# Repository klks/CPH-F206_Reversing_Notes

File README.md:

# How it started
Late 2025, I came across a Taobao listing that was selling a UHF RFID Reader for less than 10USD, this is fairly uncommon as most readers go for 15+usd onwards. I decided to buy one to add to my reader collection. (I ended up buying 6 units)<br>

<br>

This UHF RFID reader is sold under the model numbers below (with Taobao links)

- [CPH-F206](https://item.taobao.com/item.htm?id=904352296655&skuId=5763416697782)
- [TC-C206](https://item.taobao.com/item.htm?id=820590020134&skuId=5696639435762)
- [BYH-206](https://detail.tmall.com/item.htm?id=986978403603&skuId=5952377616135)

Searching online based on provided software, and screenshots, I was able to track down the company that made the software to [Cykeo](https://www.cykeorfid.com/), they are a company that specializes in making industrial rfid readers and antennas.

# Reader Software
The reader comes with its own software and SDK, and is able to output in multiple formats including Wiegand, Modbus, as well as emulating a USB Keyboard.<br>
<br>
<br>

# PCB Screenshot
Cracking open the reader, we are greeted with a 30mm x 30mm PCB soldered to a another PCB that provides a USB-C connector, a buzzer, and some led's, to keep the PCB compact, 0603 SMD components were used.<br>
<br>

Taking a closer look at the front, we see the MCU and an unknown RF chip has their markings lasered off, and the back has descriptions on what each pin does, what catches my eye is the SWDIO and SWCLK pins, this means theres Serial Wire Debug capabilities, and a chance to dump firmware.<br>
<br>
<br>

# MCU Identification & Firmware Dumping
Before we can attempt to dump the firmware, we'd need to try to figure out what MCU is used, and lucky for us when plugging in the reader the device identifies itself as a N32g43xCustom HID, this led me to believe that the MCU was a [N32G435](https://nsing.com.sg/product/General/cortexm4/N32G435/)

Connecting the SWD header to a J-LINK, setting up its parameters, and attempting to read the firmware, I was able to get a successful dump. Usually MCU's have code readout protection which prevents the downloading of flash contents, the manufacturer did not turn this feature on.

# Firmware Reversing
The firmware can now be thrown into IDA/Ghidra for analysis, using the strings within, around 70% of the firmware can be mapped back to the N32G43x SDK and example implementation found on github. From within the firmware, the RF chip can be identified, they are using an [Si4463](https://www.silabs.com/wireless/proprietary/ezradiopro-sub-ghz-ics/device.si4463?tab=specs) Transceiver chip that supports the ISM band.

<br>
The reversing of the firmware is left as an exercise for the user and will not be covered here.

# PCB Reverse Engineering
The reversing of the PCB would not be possible if the firmware dump was not successful, now that we have the firmware, my next goal is to recreate the PCB but using larger 0805 SMD components.

With PCB reversing, the first steps are component identification, using a hot-plate, components were removed one by one, and their values recorded.<br>

<br>

When dealing with small value components like inductors and capacitors, a Nano-VNA can be used to identify their values.<br>

<br>

# Parts Identification
Identification of parts took a while as finding parts with the same name was challenging. Using part numbers, a multimeter, a component tester, an oscilloscope, image searching and pouring over datasheets helped find most of the components.<br>

<br>

| Marking | Name | Notes |
| --- | ---| --- |
| N32G435 | | MCU <br> [Datasheet](https://www.nsing.com.sg/uploads/DS/EN_DS_N32G435.pdf) |
| Si4463 | | RF Transceiver <br> [Datasheet](https://www.silabs.com/documents/public/data-sheets/Si4463-61-60-C.pdf)|
| 87t | Planar Schottky barrier diode |  [1PS70SB84](https://assets.nexperia.com/documents/data-sheet/1PS70SB82_84_85_86.pdf) (Obsolete), the closest is [BAT54S](https://assets.nexperia.com/documents/data-sheet/BAT54S.pdf) |
| 1F | 45 V, 100 mA NPN/NPN general-purpose transistor | [Datasheet](https://assets.nexperia.com/documents/data-sheet/BC847BS.pdf) |
| -V4 | 2-ch, 1.65-V to 5.5-V inverters | [SN74LVC2G04](https://www.ti.com/lit/ds/symlink/sn74lvc2g04.pdf) |
| AM | NPN switching transistor | [MMBT3904](https://www.onsemi.com/pdf/datasheet/mmbt3904wt1-d.pdf) |
| G4B | RF Switching Diode | No exact match found, the closest is [BAV70](https://assets.nexperia.com/documents/data-sheet/BAV70.pdf)
| N933 | 500mA uCap Ultra-Low Dropout, High PSRR LDO Regulator | [Datasheet](https://ww1.microchip.com/downloads/aemDocuments/documents/OTH/ProductDocuments/DataSheets/500mA-uCap-Ultra-Low-Dropout-Regulator-with-High-PSRR-DS20005876B.pdf) |

For the Si4463 matching and filter network, the datasheet was used to identify the nominal values.

<br>

# Sanding PCB
After the components and their positions have been identified, the solder mask of the PCB is stripped using a 200-600 grit sandpaper to expose the front and back copper layers. This PCB is 4 layers and is 1mm thick.

<br>
<br>

# Tracing PCB
Next using high resolution images, Inkscape, and a multimeter, the traces of the PCB and its via's are drawn in separate layers<br>
This step also maps the MCU and RF pins, an overlay from the datasheet is added for pin identification. The position and values of components measured earlier are also noted, grounds and power lines (5V, 3V3) are color coded.<br>

<br>

<br>

# Reversing PCB & Schematic
Using KiCad, the schematic is then redrawn with their component values. In this step, the component names from KiCad are mapped back to the PCB Trace in Inkscape. Some modifications were made around the USB-C and 3V3 power regulators circuit.

<br>

Schematics are released in the schematic directory of this repo.

# Impedance Matching of RF Trace
When recreating the PCB, KiCad's Calculator Tools and JLCPCB's Capabilities are used to calculate trace width and spacing for the RF trace line.

<br>
<br>

# Ordering & Testing PCB
After weeks of tracing and schematic drawing, PCB's are sent for fabrication. When placing components, i mimicked the layout of the original board, this was done to make circuit debugging easier<br>
<br>
Below is a size comparison of the original and recreated PCB.<br>
<br>
After soldering all the components, the original MCU was soldered on for testing. In the first attempt, the reader was not picking up any tags.<br>
Going back to the drawing board, a few components had to be re-measured from another working reader and a few mistakes were identified. At this point an oscilloscope was used to debug the circuit using references from a functional reader. After fixing mis-typed components and much experimenting, the reader works!.<br>
<br>
One area that needs to be studied more is the matching network and filter sections as the current PCB isn't as fast/sensitive enough at picking up tags vs the original reader.<br>
In v0.2 of the schematic, additional capacitors were added to the 5V rail. Also fixed incorrectly measured value for some components.<br>

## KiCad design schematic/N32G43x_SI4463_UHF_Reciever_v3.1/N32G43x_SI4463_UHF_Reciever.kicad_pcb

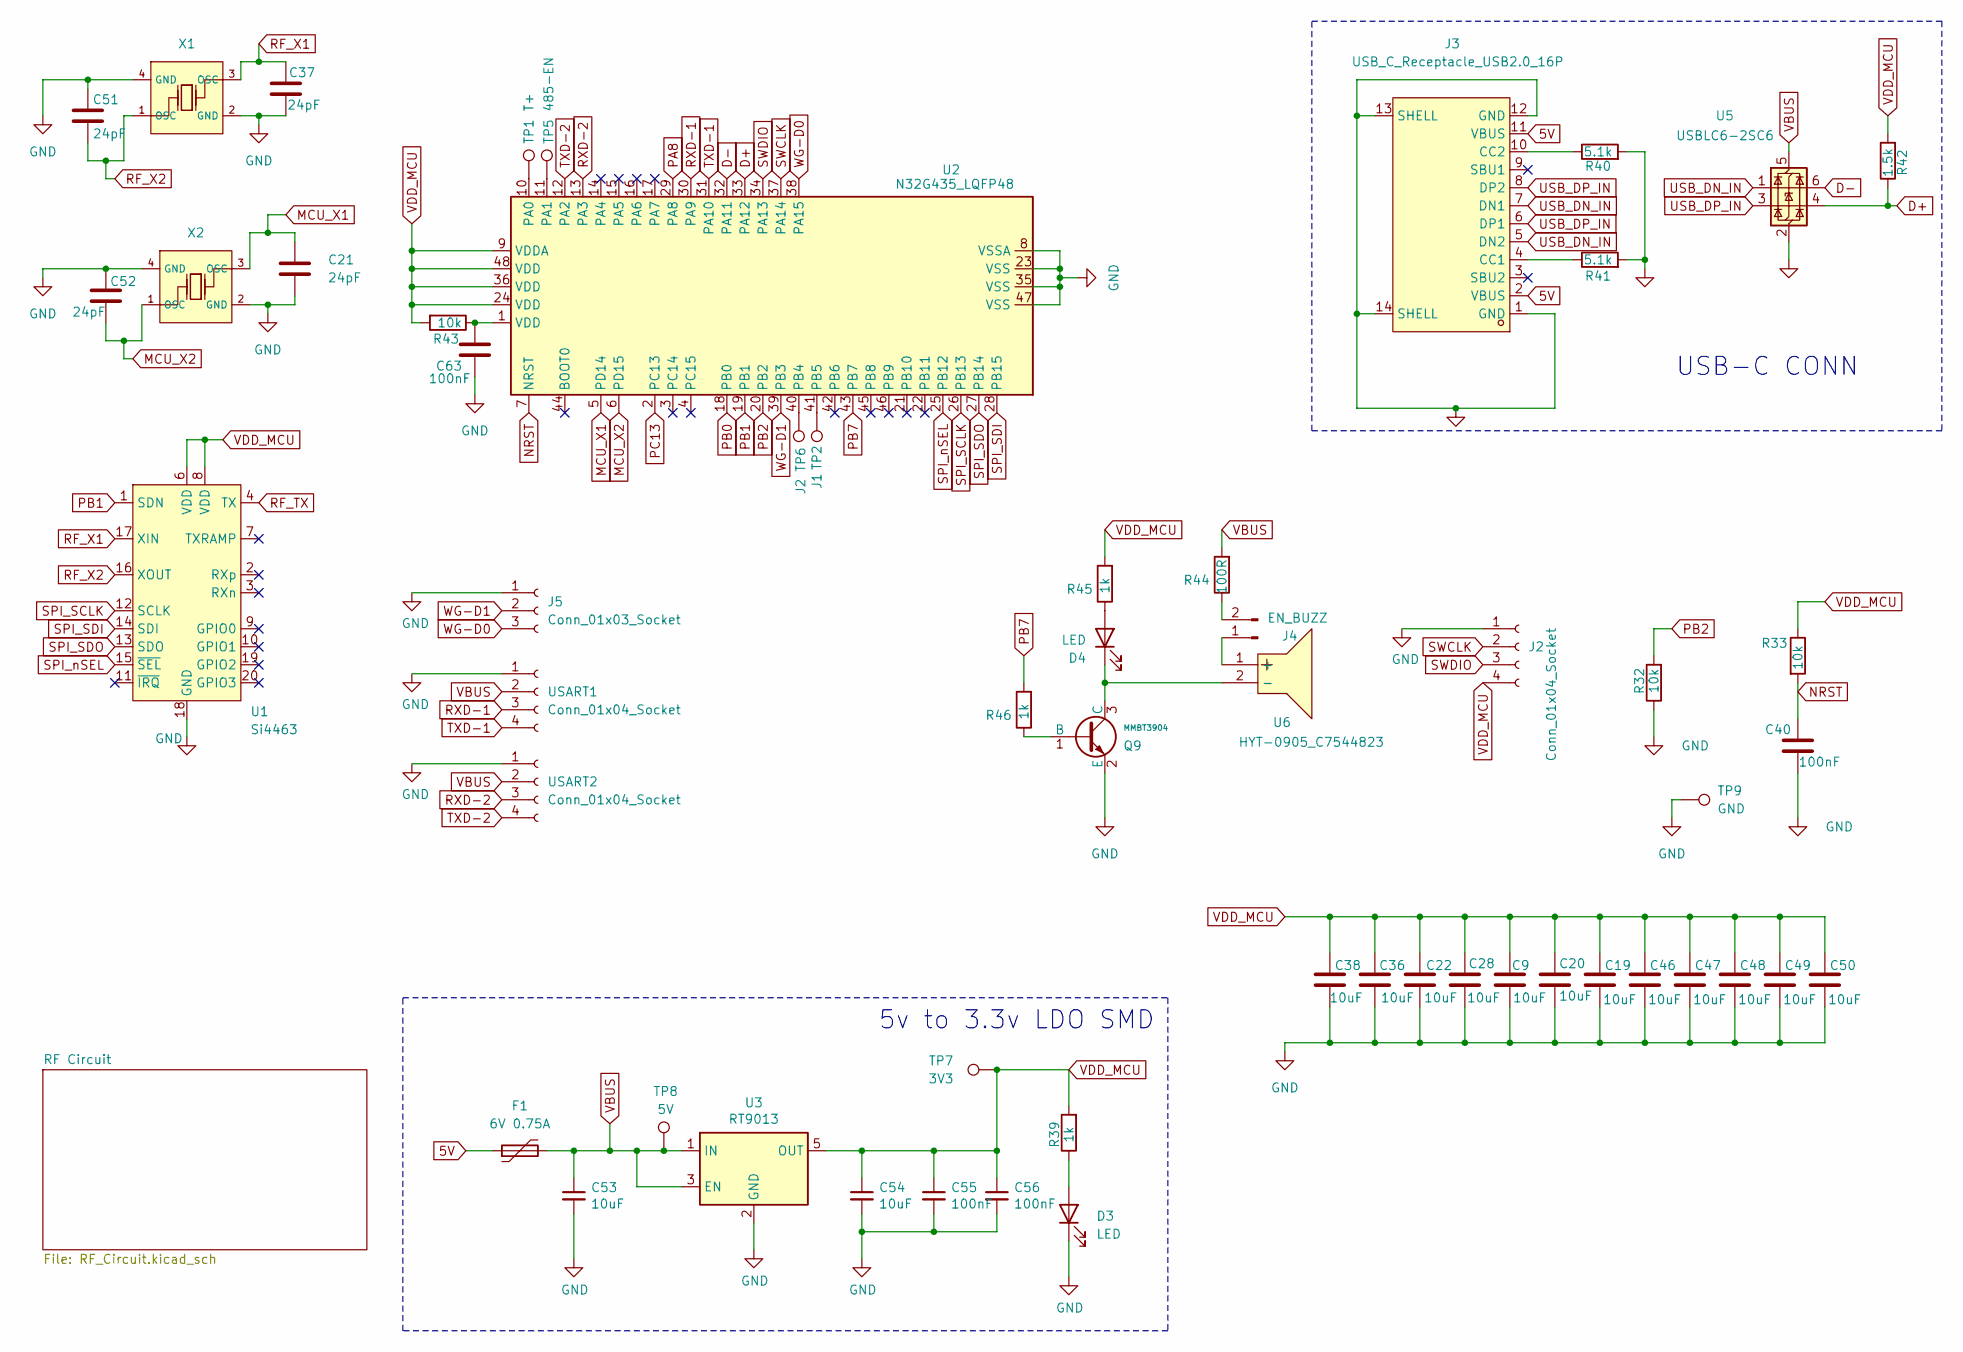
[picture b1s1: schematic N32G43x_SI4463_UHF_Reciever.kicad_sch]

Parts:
C9, C19, C20, C22, C28, C36, C38, C46, C47, C48, C49, C50, C53, C54: 10uF; C_0805_2012Metric_Pad1.18x1.45mm_HandSolder
C21, C37, C51, C52: 24pF; C_0805_2012Metric_Pad1.18x1.45mm_HandSolder
C40, C55, C56, C63: 100nF; C_0805_2012Metric_Pad1.18x1.45mm_HandSolder
D3, D4: LED; LED_0805_2012Metric_Pad1.15x1.40mm_HandSolder
F1: 6V 0.75A; Fuse_0805_2012Metric_Pad1.15x1.40mm_HandSolder
J2: Conn_01x04_Socket; PinHeader_1x04_P2.54mm_Vertical
J3: USB_C_Receptacle_USB2.0_16P; USB-C-SMD_TYPE-C-6PIN-2MD-073; LCSC Part C2765186
J4: EN_BUZZ; SolderJumper-2_P1.3mm_Open_RoundedPad1.0x1.5mm
J5: Conn_01x03_Socket; PinHeader_1x03_P2.54mm_Vertical
Q9: MMBT3904; Q_SOT-23; Part MMBT3904; LCSC C7420353
R32, R33, R43: 10k; R_0805_2012Metric_Pad1.20x1.40mm_HandSolder
R39, R45, R46: 1k; R_0805_2012Metric_Pad1.20x1.40mm_HandSolder
R40, R41: 5.1k; R_0805_2012Metric_Pad1.20x1.40mm_HandSolder
R42: 1.5k; R_0805_2012Metric_Pad1.20x1.40mm_HandSolder
R44: 100R; R_0805_2012Metric_Pad1.20x1.40mm_HandSolder
TP1: T+; TestPoint_Pad_D1.5mm
TP2: J1; TestPoint_Pad_D1.5mm
TP5: 485-EN; TestPoint_Pad_D1.5mm
TP6: J2; TestPoint_Pad_D1.5mm
TP7: 3V3; TestPoint_Pad_D1.5mm
TP8: 5V; TestPoint_Pad_D1.5mm
TP9: GND; TestPoint_Pad_D1.5mm
U1: Si4463; QFN-20-1EP_4x4mm_P0.5mm_EP2.6x2.6mm_ThermalVias
U2: N32G435_LQFP48; LQFP-48_7x7mm_P0.5mm; Operating Voltage Range 2V~3.6V; Low Voltage Detection T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 2V~3.6V; Part STM32F103C8T6; LCSC C8734
U3: RT9013; TSOP-5_1.65x3.05mm_P0.95mm
U5: USBLC6-2SC6; SOT-23-6
U6: HYT-0905_C7544823; BUZ-TH_BD9.0-P5.00-D0.6-FD; LCSC Part C7544823
USART1, USART2: Conn_01x04_Socket; PinHeader_1x04_P2.54mm_Vertical
X1, X2: X322525MOB4SI; OSC-SMD_4P-L3.2-W2.5-BL; Frequency Tolerance ±10ppm; Part X322525MOB4SI; LCSC C9006

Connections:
5V: F1.1, J3.2 (VBUS), J3.11 (VBUS)
D+: R42.1, U2.33 (PA12), U5.4 (I/O2)
D-: U2.32 (PA11), U5.6 (I/O1)
MCU_X1: C21.1, U2.5 (PD14), X2.3 (OSC)
MCU_X2: C52.2, U2.6 (PD15), X2.1 (OSC)
NRST: C40.2, R33.2, U2.7 (NRST)
unnamed: C63.1, R43.1, U2.1 (VDD)
unnamed: D3.2 (A), R39.1
unnamed: D4.2 (A), R45.1
unnamed: D4.1 (K), Q9.3 (C), U6.2 (-)
unnamed: J3.4 (CC1), R41.1
unnamed: J3.10 (CC2), R40.1
unnamed: J4.1, U6.1 (+)
unnamed: J4.2, R44.1
unnamed: Q9.1 (B), R46.1
unnamed: TP1.1, U2.10 (PA0)
unnamed: TP5.1, U2.11 (PA1)
unnamed: TP6.1, U2.40 (PB4)
unnamed: TP2.1, U2.41 (PB5)
PA8: U2.29 (PA8); also elsewhere on the board
PB0: U2.18 (PB0); also elsewhere on the board
PB1: U1.1 (SDN), U2.19 (PB1)
PB2: R32.2, U2.20 (PB2)
PB7: R46.2, U2.43 (PB7)
PC13: U2.2 (PC13); also elsewhere on the board
RF_TX: U1.4 (TX); also elsewhere on the board
RF_X1: C37.1, U1.17 (XIN), X1.3 (OSC)
RF_X2: C51.2, U1.16 (XOUT), X1.1 (OSC)
RXD-1: U2.30 (PA9), USART1.3
RXD-2: U2.13 (PA3), USART2.3
SPI_SCLK: U1.12 (SCLK), U2.26 (PB13)
SPI_SDI: U1.14 (SDI), U2.28 (PB15)
SPI_SDO: U1.13 (SDO), U2.27 (PB14)
SPI_nSEL: U1.15 (~SEL), U2.25 (PB12)
SWCLK: J2.2, U2.37 (PA14)
SWDIO: J2.3, U2.34 (PA13)
TXD-1: U2.31 (PA10), USART1.4
TXD-2: U2.12 (PA2), USART2.4
USB_DN_IN: J3.5 (DN2), J3.7 (DN1), U5.1 (I/O1)
USB_DP_IN: J3.6 (DP1), J3.8 (DP2), U5.3 (I/O2)
VBUS: C53.1, F1.2, R44.2, TP8.1, U3.1 (IN), U3.3 (EN), U5.5 (VBUS), USART1.2, USART2.2; also elsewhere on the board
VDD_MCU: C9.2, C19.1, C20.1, C22.1, C28.2, C36.1, C38.1, C46.1, C47.1, C48.1, C49.1, C50.1, C54.1, C55.1, C56.1, J2.4, R33.1, R39.2, R42.2, R43.2, R45.2, TP7.1, U1.6 (VDD), U1.8 (VDD), U2.9 (VDDA), U2.24 (VDD), U2.36 (VDD), U2.48 (VDD), U3.5 (OUT); also elsewhere on the board
WG-D0: J5.3, U2.38 (PA15)
WG-D1: J5.2, U2.39 (PB3)

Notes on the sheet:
5v to 3.3v LDO SMD
USB-C CONN

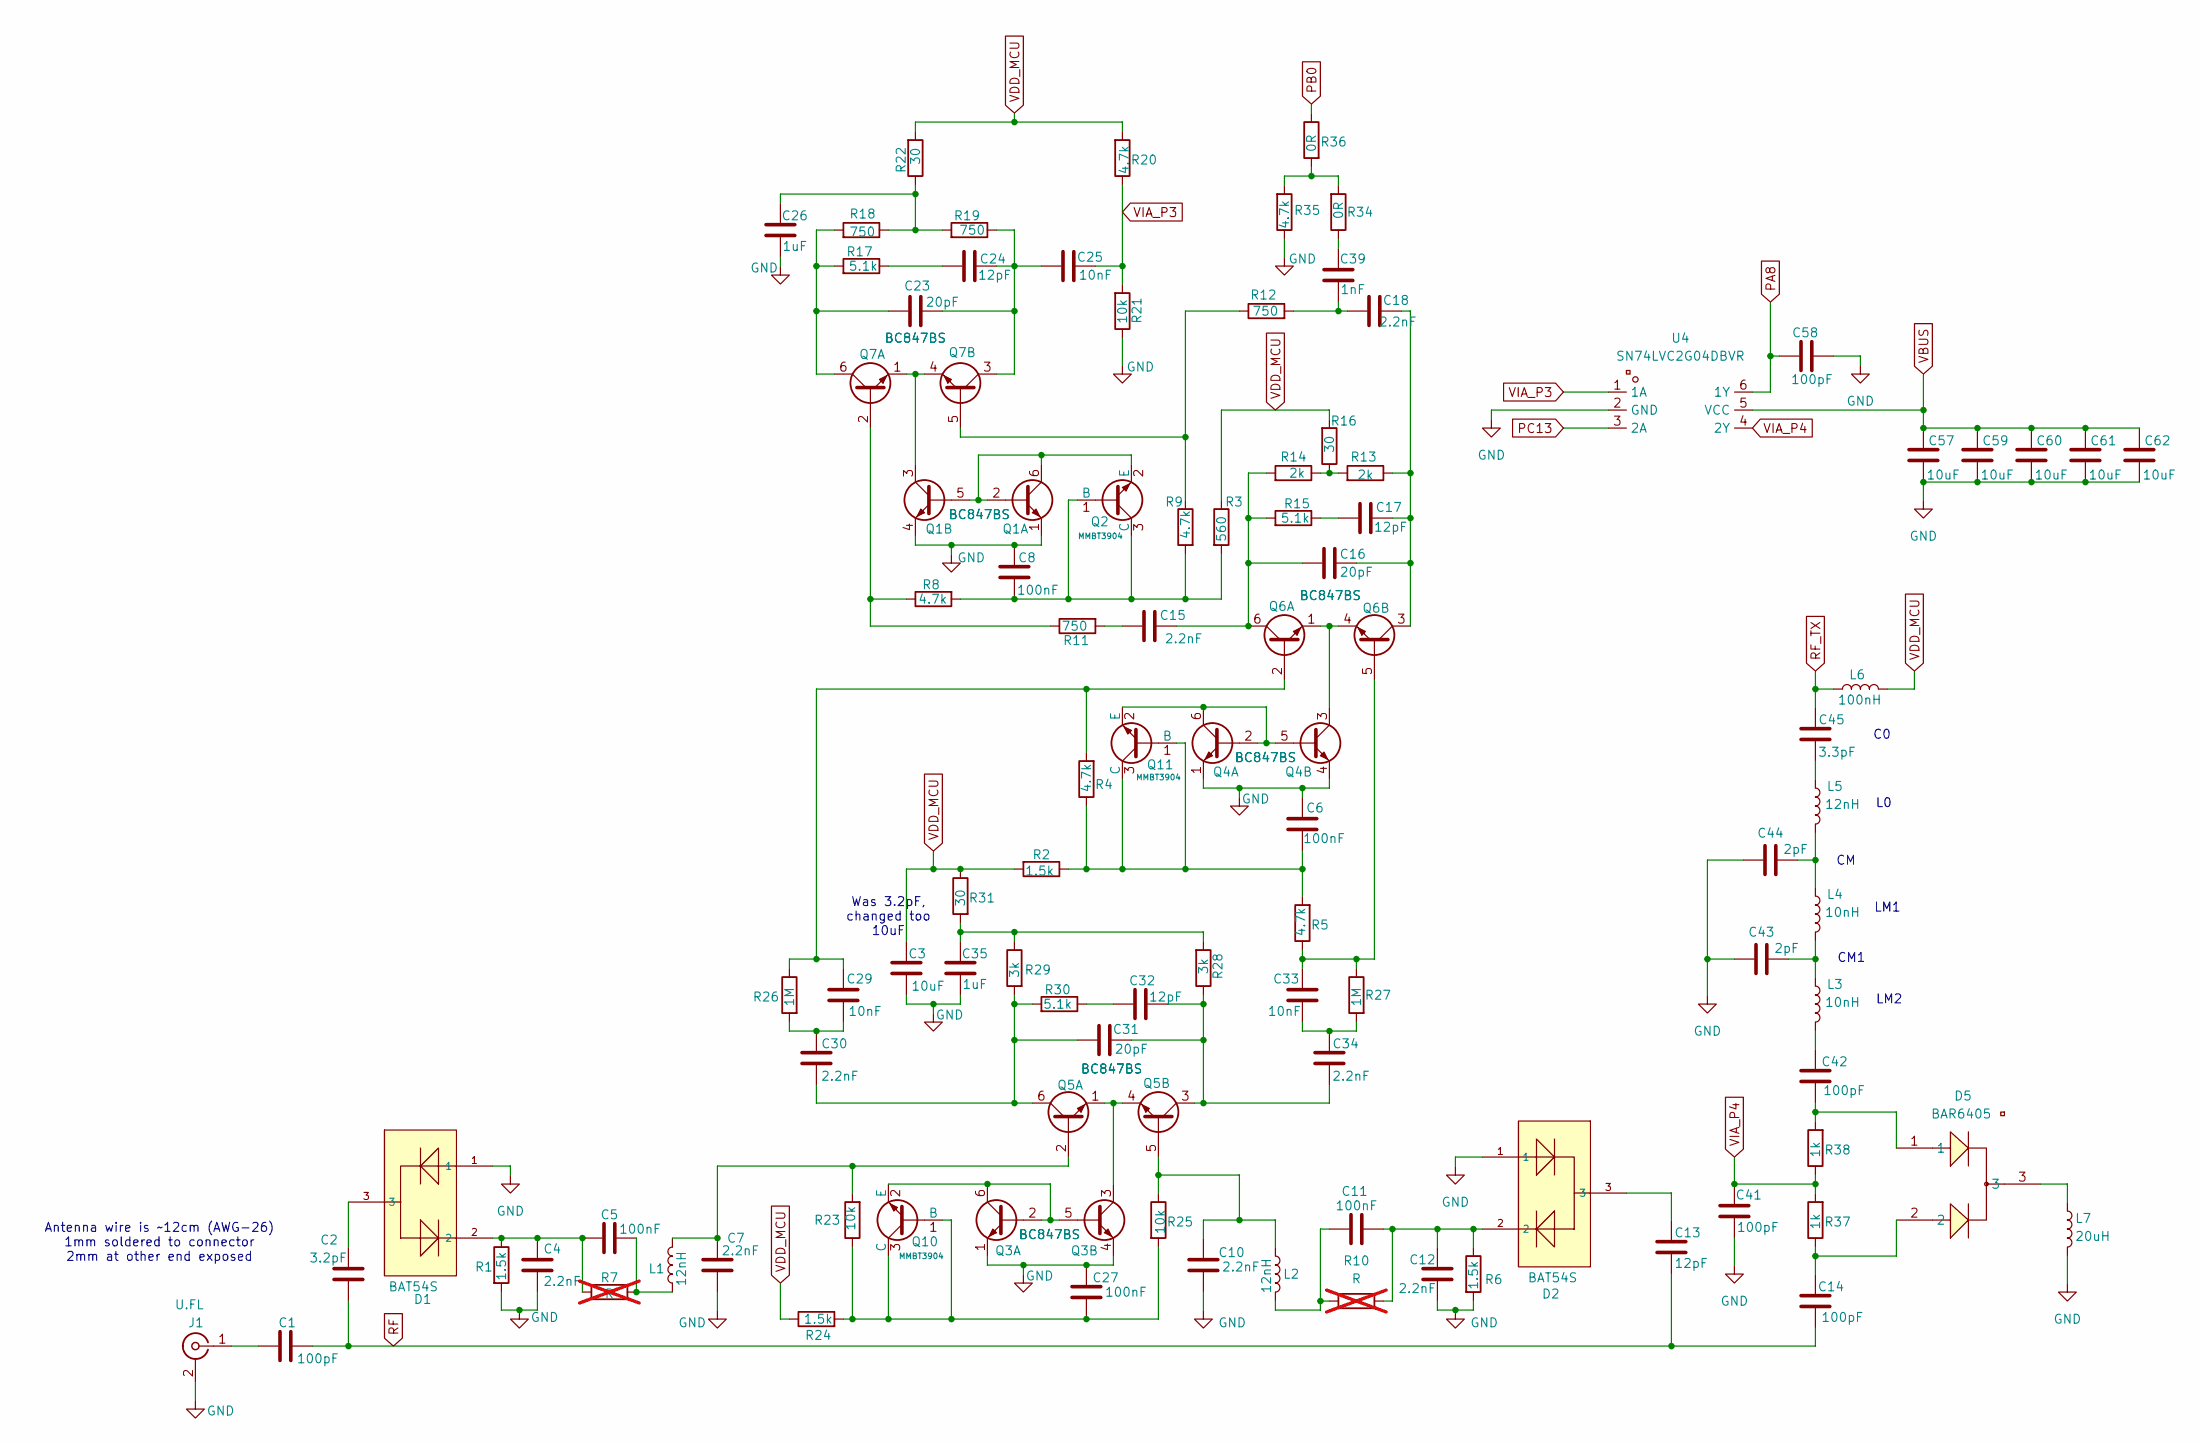
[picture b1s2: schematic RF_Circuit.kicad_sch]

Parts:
C1, C14, C41, C42, C58: 100pF; C_0805_2012Metric_Pad1.18x1.45mm_HandSolder
C2: 3.2pF; C_0805_2012Metric_Pad1.18x1.45mm_HandSolder
C3: 10uF; C_0805_2012Metric_Pad1.18x1.45mm_HandSolder
C4, C7, C10, C12, C15, C18, C30, C34: 2.2nF; C_0805_2012Metric_Pad1.18x1.45mm_HandSolder
C5, C6, C8, C11, C27: 100nF; C_0805_2012Metric_Pad1.18x1.45mm_HandSolder
C13, C17, C24, C32: 12pF; C_0805_2012Metric_Pad1.18x1.45mm_HandSolder
C16, C23, C31: 20pF; C_0805_2012Metric_Pad1.18x1.45mm_HandSolder
C25, C29, C33: 10nF; C_0805_2012Metric_Pad1.18x1.45mm_HandSolder
C26, C35: 1uF; C_0805_2012Metric_Pad1.18x1.45mm_HandSolder
C39: 1nF; C_0805_2012Metric_Pad1.18x1.45mm_HandSolder
C43, C44: 2pF; C_0805_2012Metric_Pad1.18x1.45mm_HandSolder
C45: 3.3pF; C_0805_2012Metric_Pad1.18x1.45mm_HandSolder
C57, C59, C60, C61, C62: 10uF; C_1206_3216Metric_Pad1.33x1.80mm_HandSolder
D1, D2: BAT54S; SOT-23-3_L2.9-W1.6-P1.90-LS2.8-BR; Reverse Voltage (Vr) 100V; Forward Voltage (Vf@If) 1.25V@150mA; Part BAV99,215
D5: BAR6405; SOT-23-3_L2.9-W1.6-P1.90-LS2.8-BR
J1: U.FL; IPEX-SMD_BWIPX-1-001E; LCSC C5137195
L1, L2, L5: 12nH; L_0805_2012Metric_Pad1.05x1.20mm_HandSolder
L3, L4: 10nH; L_0805_2012Metric_Pad1.05x1.20mm_HandSolder
L6: 100nH; L_0805_2012Metric_Pad1.05x1.20mm_HandSolder
L7: 20uH; L_0805_2012Metric_Pad1.05x1.20mm_HandSolder
Q1, Q3, Q4, Q5, Q6, Q7: BC847BS; SOT-363_SC-70-6; Part BC847BS; LCSC C41375126
Q2, Q10, Q11: MMBT3904; Q_SOT-23; Part MMBT3904; LCSC C7420353
R1, R2, R6, R24: 1.5k; R_0805_2012Metric_Pad1.20x1.40mm_HandSolder
R3: 560; R_0805_2012Metric_Pad1.20x1.40mm_HandSolder
R4, R5, R8, R9, R20, R35: 4.7k; R_0805_2012Metric_Pad1.20x1.40mm_HandSolder
R7, R10: R; R_0805_2012Metric_Pad1.20x1.40mm_HandSolder; not fitted
R11, R12, R18, R19: 750; R_0805_2012Metric_Pad1.20x1.40mm_HandSolder
R13, R14: 2k; R_0805_2012Metric_Pad1.20x1.40mm_HandSolder
R15, R17, R30: 5.1k; R_0805_2012Metric_Pad1.20x1.40mm_HandSolder
R16, R22, R31: 30; R_0805_2012Metric_Pad1.20x1.40mm_HandSolder
R21, R23, R25: 10k; R_0805_2012Metric_Pad1.20x1.40mm_HandSolder
R26, R27: 1M; R_0805_2012Metric_Pad1.20x1.40mm_HandSolder
R28, R29: 3k; R_0805_2012Metric_Pad1.20x1.40mm_HandSolder
R34, R36: 0R; R_0805_2012Metric_Pad1.20x1.40mm_HandSolder
R37, R38: 1k; R_0805_2012Metric_Pad1.20x1.40mm_HandSolder
U4: SN74LVC2G04DBVR; SOT-23-6_L2.9-W1.6-P0.95-LS2.8-BR; LCSC Part C10428

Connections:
unnamed: C2.2, D1.3
unnamed: C4.2, C5.2, D1.2, R1.1, R7.1
unnamed: C5.1, L1.1, R7.2
unnamed: C11.1, C12.2, D2.2, R6.1, R10.2
unnamed: C11.2, L2.2, R10.1
unnamed: C13.2, D2.3
unnamed: C14.1, D5.2, R37.1
unnamed: C15.2, R11.2
unnamed: C17.1, R15.1
unnamed: C18.2, C39.2, R12.2
unnamed: C24.1, R17.1
unnamed: C26.1, R18.1, R19.2, R22.1
unnamed: C29.1, C30.2, R26.2
unnamed: C32.1, R30.1
unnamed: C33.1, C34.2, R27.2
unnamed: C35.1, R28.2, R29.1, R31.2
unnamed: C39.1, R34.1
unnamed: C42.1, L3.2
unnamed: C42.2, D5.1, R38.2
unnamed: C43.1, L3.1, L4.2
unnamed: C44.1, L4.1, L5.2
unnamed: C45.2, L5.1
unnamed: D5.3, L7.1
unnamed: C1.2, J1.1 (In)
unnamed: Q1.2 (B1), Q1.5 (B2), Q1.6 (C1), Q2.2 (E)
unnamed: Q1.3 (C2), Q7.1 (E1), Q7.4 (E2)
unnamed: C8.1, Q2.1 (B), Q2.3 (C), R3.2, R8.2, R9.2
unnamed: Q3.3 (C2), Q5.1 (E1), Q5.4 (E2)
unnamed: Q4.3 (C2), Q6.1 (E1), Q6.4 (E2)
unnamed: C7.2, L1.2, Q5.2 (B1), R23.2
unnamed: C30.1, C31.1, Q5.6 (C1), R29.2, R30.2
unnamed: C10.2, L2.1, Q5.5 (B2), R25.1
unnamed: C31.2, C32.2, C34.1, Q5.3 (C2), R28.1
unnamed: C29.2, Q6.2 (B1), R4.2, R26.1
unnamed: C15.1, C16.1, Q6.6 (C1), R14.2, R15.2
unnamed: C33.2, Q6.5 (B2), R5.1, R27.1
unnamed: C16.2, C17.2, C18.1, Q6.3 (C2), R13.1
unnamed: Q7.2 (B1), R8.1, R11.1
unnamed: C23.1, Q7.6 (C1), R17.2, R18.2
unnamed: Q7.5 (B2), R9.1, R12.1
unnamed: C23.2, C24.2, C25.1, Q7.3 (C2), R19.1
unnamed: C27.2, Q10.1 (B), Q10.3 (C), R23.1, R24.2, R25.2
unnamed: Q3.2 (B1), Q3.5 (B2), Q3.6 (C1), Q10.2 (E)
unnamed: C6.1, Q11.1 (B), Q11.3 (C), R2.1, R4.1, R5.2
unnamed: Q4.2 (B1), Q4.5 (B2), Q4.6 (C1), Q11.2 (E)
unnamed: R13.2, R14.1, R16.1
unnamed: R34.2, R35.2, R36.2
PA8: C58.1, U4.6 (1Y); also elsewhere on the board
PB0: R36.1; also elsewhere on the board
PC13: U4.3 (2A); also elsewhere on the board
RF: C1.1, C2.1, C13.1, C14.2
RF_TX: C45.1, L6.1; also elsewhere on the board
VBUS: C57.1, C59.1, C60.1, C61.1, C62.1, U4.5 (VCC); also elsewhere on the board
VDD_MCU: C3.2, L6.2, R2.2, R3.1, R16.2, R20.2, R22.2, R24.1, R31.1; also elsewhere on the board
VIA_P3: C25.2, R20.1, R21.2, U4.1 (1A)
VIA_P4: C41.1, R37.2, R38.1, U4.4 (2Y)

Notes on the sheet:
LM1
LM2
Was 3.2pF, changed too 10uF
Antenna wire is ~12cm (AWG-26) 1mm soldered to connector 2mm at other end exposed
CM1

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
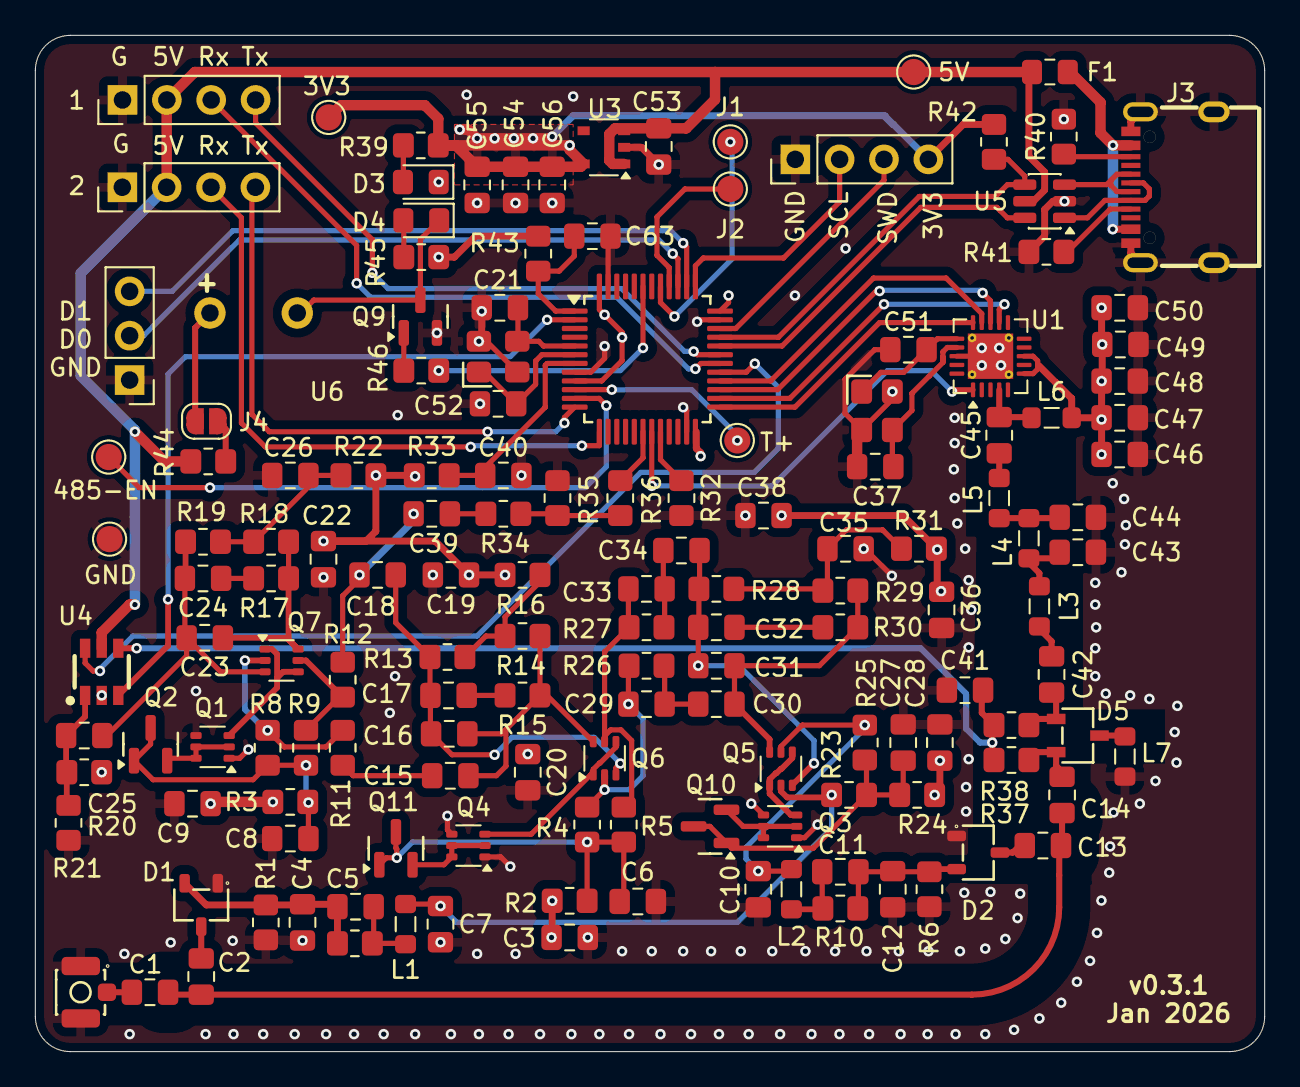
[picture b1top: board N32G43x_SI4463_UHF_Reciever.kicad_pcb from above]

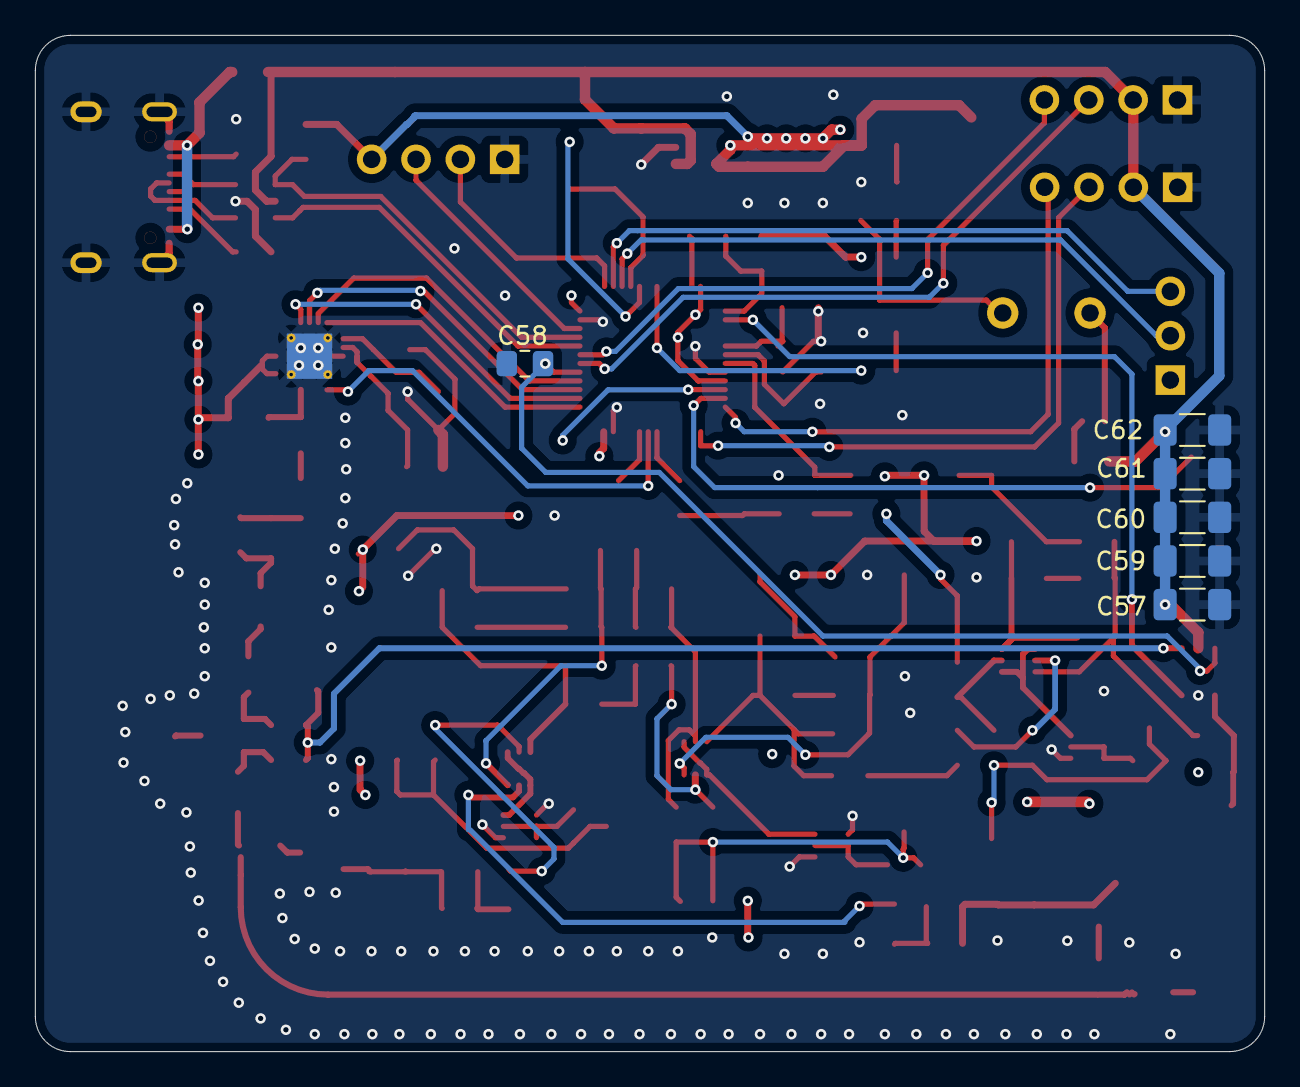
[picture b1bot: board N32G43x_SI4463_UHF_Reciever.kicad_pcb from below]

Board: 4 copper layers, 70.4 x 58.2 mm, 154 parts (6 on the bottom side), 95 nets.

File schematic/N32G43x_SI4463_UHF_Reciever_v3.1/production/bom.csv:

Designator,Footprint,Quantity,Value,LCSC Part #
"C1, C14, C41, C42, C58",0805,5,100pF,
"C10, C12, C15, C18, C30, C34, C4, C7",0805,8,2.2nF,
"C11, C27, C40, C5, C55, C56, C6, C63, C8",0805,9,100nF,
"C13, C17, C24, C32",0805,4,12pF,
"C16, C23, C31",0805,3,20pF,
"C19, C20, C22, C28, C3, C36, C38, C46, C47, C48, C49, C50, C53, C54, C9",0805,15,10uF,
C2,0805,1,3.2pF,
"C21, C37, C51, C52",0805,4,24pF,
"C25, C29, C33",0805,3,10nF,
"C26, C35",0805,2,1uF,
C39,0805,1,1nF,
"C43, C44",0805,2,2pF,
C45,0805,1,3.3pF,
"C57, C59, C60, C61, C62",1206,5,10uF,
"D1, D2",SOT-23-3_L2.9-W1.6-P1.90-LS2.8-BR,2,BAT54S,
"D3, D4",0805,2,LED,
D5,SOT-23-3_L2.9-W1.6-P1.90-LS2.8-BR,1,BAR6405,
F1,0805,1,6V 0.75A,
J1,IPEX-SMD_BWIPX-1-001E,1,U.FL,C5137195
"J2, USART1, USART2",PinHeader_1x04_P2.54mm_Vertical,3,Conn_01x04_Socket,
J3,USB-C-SMD_TYPE-C-6PIN-2MD-073,1,USB_C_Receptacle_USB2.0_16P,C2765186
J4,SolderJumper-2_P1.3mm_Open_RoundedPad1.0x1.5mm,1,EN_BUZZ,
J5,PinHeader_1x03_P2.54mm_Vertical,1,Conn_01x03_Socket,
"L1, L2, L5",0805,3,12nH,
"L3, L4",0805,2,10nH,
L6,0805,1,100nH,
L7,0805,1,20uH,
"Q1, Q3, Q4, Q5, Q6, Q7",SOT-363_SC-70-6,6,BC847BS,C41375126
"Q10, Q11, Q2, Q9",Q_SOT-23,4,MMBT3904,C7420353
"R1, R2, R24, R42, R6",0805,5,1.5k,
"R10, R7",0805,2,R,
"R11, R12, R18, R19",0805,4,750,
"R13, R14",0805,2,2k,
"R15, R17, R30, R40, R41",0805,5,5.1k,
"R16, R22, R31",0805,3,30,
"R20, R35, R4, R5, R8, R9",0805,6,4.7k,
"R21, R23, R25, R32, R33, R43",0805,6,10k,
"R26, R27",0805,2,1M,
"R28, R29",0805,2,3k,
R3,0805,1,560,
"R34, R36",0805,2,0R,
"R37, R38, R39, R45, R46",0805,5,1k,
R44,0805,1,100R,
TP1,TestPoint_Pad_D1.5mm,1,T+,
TP2,TestPoint_Pad_D1.5mm,1,J1,
TP5,TestPoint_Pad_D1.5mm,1,485-EN,
TP6,TestPoint_Pad_D1.5mm,1,J2,
TP7,TestPoint_Pad_D1.5mm,1,3V3,
TP8,TestPoint_Pad_D1.5mm,1,5V,
TP9,TestPoint_Pad_D1.5mm,1,GND,
U1,QFN-20-1EP_4x4mm_P0.5mm_EP2.6x2.6mm_ThermalVias,1,Si4463,
U2,LQFP-48_7x7mm_P0.5mm,1,N32G435_LQFP48,C8734
U3,TSOP-5_1.65x3.05mm_P0.95mm,1,RT9013,
U4,SOT-23-6_L2.9-W1.6-P0.95-LS2.8-BR,1,SN74LVC2G04DBVR,C10428
U5,SOT-23-6,1,USBLC6-2SC6,
U6,BUZ-TH_BD9.0-P5.00-D0.6-FD,1,HYT-0905_C7544823,C7544823
"X1, X2",OSC-SMD_4P-L3.2-W2.5-BL,2,X322525MOB4SI,C9006

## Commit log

2025-12-27 Minor updates
2025-12-28 schematic rework
    reworked main schematic for readability.
    reworked RF schematic for readability, with annotations
    switched out custom footprints to kicad footprints when they exist in the default kicad libraries
2026-01-11 Minor update to match pcb
2026-01-12 Added notes for BAV70
2026-01-14 Update some IC's and fix typos
2026-01-14 Add info on 87t
